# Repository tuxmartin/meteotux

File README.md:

meteotux
========

<!--
Screenshot weboveho rozhranni:
-

-->

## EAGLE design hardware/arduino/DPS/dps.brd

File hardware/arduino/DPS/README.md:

# !!! Stabilizator 7805 je obracene !!! #
Je potreba ho pri pajeni otocit (krajni dva piny).

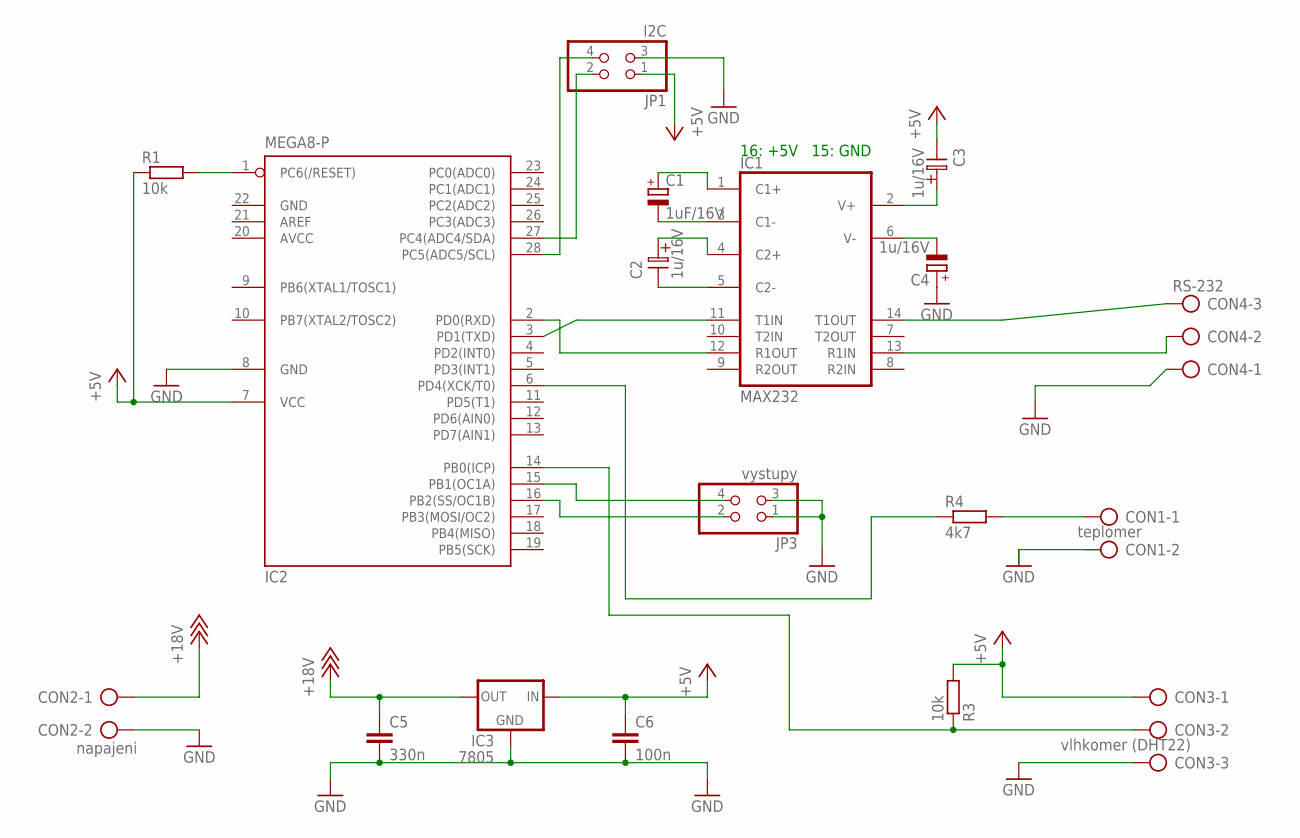
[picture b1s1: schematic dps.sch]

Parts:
C1: 1uF/16V; TT5D9
C2, C3: 1u/16V; ES-2,5L
C4: 1u/16V; TT5D9
C5: 330n; C025-025X050
C6: 100n; C025-025X050
CON1: teplomer; AK500/2
CON2: napajeni; AK500/2
CON3: vlhkomer (DHT22); AK500/3
CON4: RS-232; AK500/3
IC1: MAX232; DIL16
IC2: MEGA8-P; DIL28-3
IC3: 7805; 78XXL
JP1: I2C; 2X02
JP3: vystupy; 2X02
R1, R3: 10k; 0207/7
R4: 4k7; 0207/15

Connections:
+5V: C3.2, C6.1, CON3.1, IC1.16 (VCC), IC2.7 (VCC), IC3.IN, JP1.1, R1.1, R3.2
+18V: C5.1, CON2.1, IC3.OUT
AVCC: IC2.20 (AVCC)
GND: C4.+, C5.2, C6.2, CON2.2, CON3.3, CON4.1, IC1.15 (GND), IC2.8 (GND), IC2.22 (GND), IC3.GND, JP1.3, JP3.1, JP3.3
unnamed: IC1.12 (R1OUT), IC2.2 (PD0(RXD))
unnamed: C1.+, IC1.1 (C1+)
unnamed: C1.-, IC1.3 (C1-)
unnamed: C2.1, IC1.4 (C2+)
unnamed: C2.2, IC1.5 (C2-)
unnamed: C3.1, IC1.2 (V+)
unnamed: C4.-, IC1.6 (V-)
unnamed: IC1.11 (T1IN), IC2.3 (PD1(TXD))
unnamed: CON4.3, IC1.14 (T1OUT)
unnamed: CON4.2, IC1.13 (R1IN)
unnamed: IC2.28 (PC5(ADC5/SCL)), JP1.4
unnamed: CON1.1, R4.2
unnamed: IC2.16 (PB2(SS/OC1B)), JP3.2
unnamed: IC2.15 (PB1(OC1A)), JP3.4
unnamed: IC2.6 (PD4(XCK/T0)), R4.1
unnamed: IC2.27 (PC4(ADC4/SDA)), JP1.2
unnamed: CON3.2, IC2.14 (PB0(ICP)), R3.1
unnamed: IC2.1 (PC6(/RESET)), R1.2

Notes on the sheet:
16: +5V 15: GND

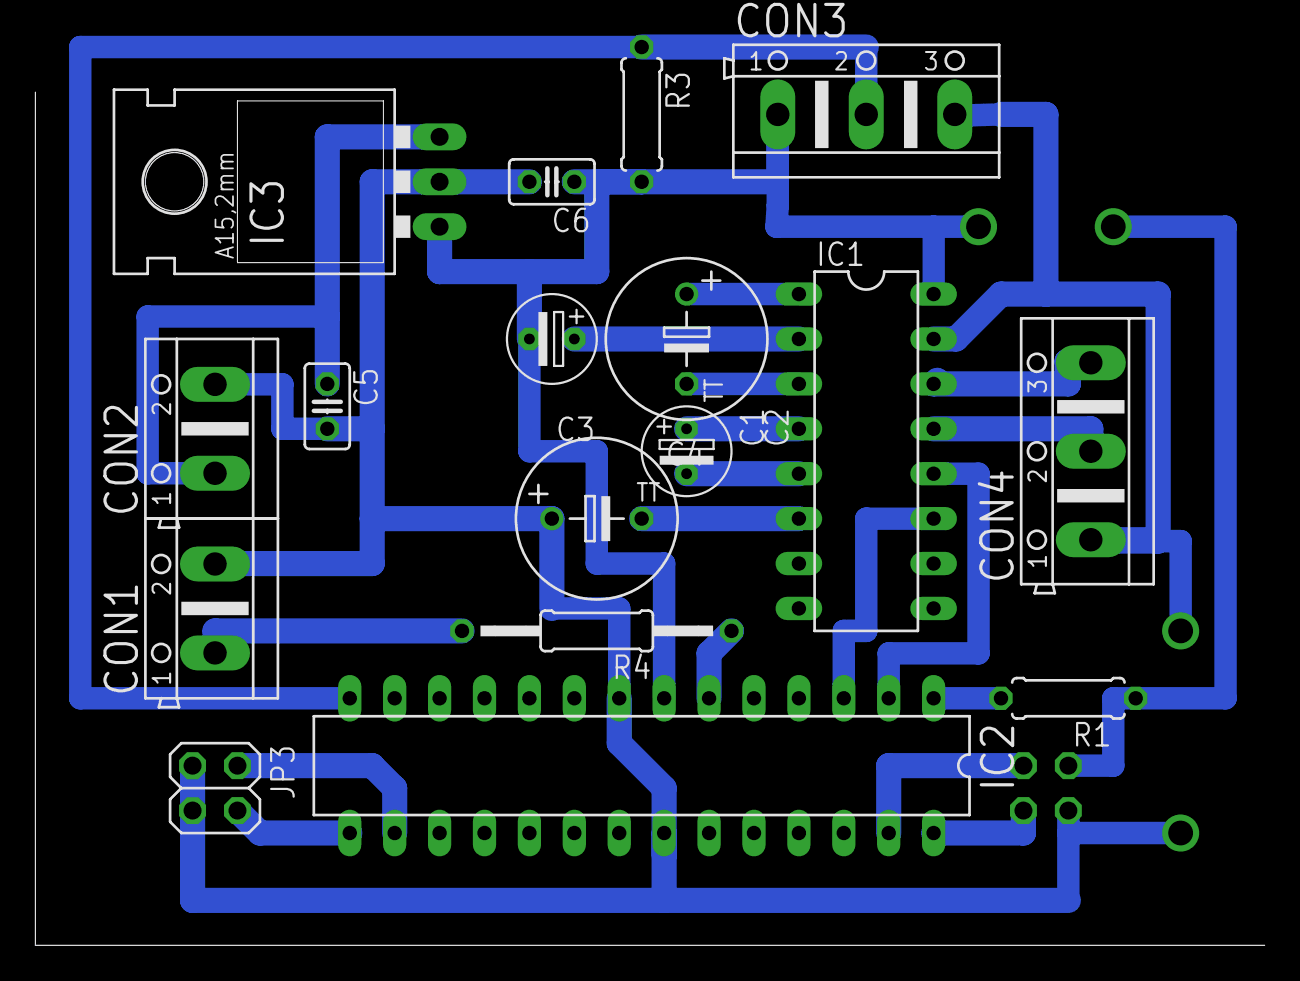
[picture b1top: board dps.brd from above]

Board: 2 copper layers, 69.5 x 48.2 mm, 18 parts (1 on the bottom side), 21 nets.

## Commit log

2013-02-12 +gitignore pro C, C++, Java
    Vice na https://github.com/github/gitignore
2013-02-12 +Jabber klient a SMACK xmpp knihovna
2013-02-12 +kod na komunikaci se seriovym portem (RS-232)
2013-02-12 +RSS (nacita hodnotu ze souboru)
2013-02-12 +skript na pasrsovani teploty z TMEP weboveho teplomeru
    http://code.google.com/p/tmep/
2013-02-22 +kod a ukazky pro arduino (prevzate z jineho projektu)
2013-02-22 OneWire knihovna nefunguje s novym Arduino IDE 1.0.1
2013-02-22 +DHT22 ukazkova knihovna: vlhkost a teplota OK
2013-02-22 format vypisu DHT-22 do RS-232 "23.10C 36.40%"
2013-02-22 funguje nekonecne cteni a vypisovani namerenych hodnot
2013-02-22 uprava nactenych hodnot a jejich rozdeleni do pole
2013-02-22 funguje nastaveni XMPP (Jabber) statusu s hodnotami
2013-02-22 kdyz jeste nejsou zmerene hodnoty, neaktualizuje status
2013-02-22 pomocny skript pro pripojeni projektu na localhost webserveru
2013-02-22 +sql tabulka pro ukladani namerenych hodnot
2013-02-23 +pridavani zaznamu pres URL do MySQL a zobrazeni vysledku
2013-02-23 +RSS - zobrazuje: teplota, vlhkost, teplota+vlhkost
2013-02-23 +www stranka s prehledem pocasi (vcetne RSS)
    historie, max, min, celkovy pocet, ...
2013-02-23 OK: mereni, XMPP aktualizace, HTTP aktualizace (do MySQL)
2013-02-23 zmenseni sloupce s rekordy
2013-02-23 +screenshot webove rozhranni
2013-02-23 chyba v SQL dotazu - spatne zobrazeni rekordnich teplot
2013-02-23 +navod na pouzit TMEP web app
2013-02-23 +podpora pro TMEP web app
2013-02-23 nalezena chyba v SQL dotazu pro hledani max teploty
2013-02-23 xmppClient - odstranen debug vypis na konzolu (sysout)
2013-02-23 +navod na spusteni vysledneho JAR souboru (je potreba JNI)
2013-02-24 Test odeslani dat do TMEP app. Overeni spravneho user-agenta.
2013-02-24 Prechod z Java 1.7 na Java 1.6: Debian stable nema Java 1.7.
2013-02-24 oprava komunikace s TMEP (poslani jineho http user-agenta)
2013-02-24 opraven preklep v komentari
2013-02-24 Odstranena knihovna Apache CommonsIO - nikde nebyla pouzita.
2013-02-24 +JAR soubory knihovny smack (xmpp), ktere kvuli gitignore chybely
2013-02-25 opraven komentar popisuju jeste neopravenou chybu (SQL MAX)
2013-03-01 phpinfo pro otestovani php curl modulu
2013-03-01 volani TMEP pres curl
2013-03-01 +diff pro TMEP 6.1 - posilani hodnoty jen z localhostu
    TMEP nepobezi v PC s teplomerem, ale na webhostingu.
    Protoze PC s teplomerem nebude mit verjenou IPv4 adresu,
    bylo by nutne vypnout v TMEPu kontrolu IP - za chvili by
    nam nekdo udelal v namerenych hodnotach pekny bordel...
    Proto TMEP prijima hodnoty pouze z localhostu a dalsi
    skript "teplota.php" na localhostu (webhostingu) bude
2013-03-01 +komentar k overovani IP u TMEP web app
2013-03-02 +firmware pro 8MHz ATmega8; optiboot zavadec; uprava Arduino IDE
2013-03-02 +schema plosneho spoje - nutno jeste zkontrolovat!
2013-03-10 program uz nevola TMEP, to si resi php aplikace
2013-03-10 nastaveni presunuto do samostatneho INI souboru
2013-05-20 +prejmenovana app v Jave, bude nasledovat app v Pythonu
2013-05-20 zaklad app v pythonu - nevyzkouseno!!!
2013-05-21 +APP (widget) pro Android. Funguje stazeni TXT pres HTTP a zobrazeni ve widgetu.
2013-05-21 upraveny widget pro pouziti http://teplomer.jicin.cz/
2013-05-21 pozadi z pruhledne na bilou - nebyl videt text
2013-05-21 funguje spravne cteni a vypisovani hodnot na stdout
2013-05-21 funguje posilani webove aplikaci; opravit neustale pridavani casu!
2013-05-21 webovy vystup pro android widget
2013-05-21 zpracovani vysledku v samostanem vlakne (kvuli zpozdeni mereni)
    bez druheho vlakna se prodluzovala doba mezi merenimi - cekalo se na
    dokonceni http pozadavku
2013-06-10 +logovani do syslogu
2013-06-10 oprava odsazeni radku syslogu
2013-07-15 -duplicitni ukladani do DB
2013-07-15 +komprese RSS - mensi prenos dat pro mobily
2013-07-15 hodnoty z TMEP tabulky; prechod na RSS2.0, vyhazeni zbytecnych elementu (mensi prenos dat)
2013-07-15 -tabulky z "index", nyni pouze odkaz a navod na RSS pro Andoid
2013-07-17 -skript neuklada datum poslane zarizenim
2013-07-17 +diff pro novy TMEP v6.3; -diff pro TMEP v 6.1
2013-07-17 +test odeslani teploty primo do TMEP bez meho skriptu
2013-07-17 +ve verzi bez parametru vraci RSS cas (hodiny a minuty)
2013-07-17 pridana chybejici mezera pred hodiny
2013-07-17 +ukazka widgetu na Android mobilu
2013-07-19 +stranka s boxem aktualnich hodnot - taha je z TMEP
    bude slouzit pro zobrazeni na webu v iframe
    pouziva curl :-/
2013-07-24 opravena verze plosneho spoje (cti README!!!)
    ve stare verzi byl spatne odpor z reset pinu ATmega8 (pin 1) na zem, spravne ma byt na +5V
    v nove verzi je obracene stabilizator 7805!!! a to jak ve schematu, tak na plosnem spoji - je nutne ho pri pajeni obratit !!!
2013-07-24 -screenshot stare verze webove rozhranni
2013-07-29 +funkcni verze pro OpenWrt (mereni a watchdog)
2013-08-01 +navod na Windows 7 gadget
2013-11-26 Kvuli chybe v DHT knihovne vracel pro zaporne teploty 32767.
    Chyba v pouzite DHT22 knihovne vraci pokud je namerena teplota mensi, nez 0°C "MAX_INT - namerenou teplotu". MAX_INT je na Arduinu 2 bajty = 32767 http://arduino.cc/en/Reference/Int
    Pro opravu lze vypocitat spravnou hodnotu.
    Napr. pro cislo 3276,4°C je teplota -0,3°C.
    TODO: opravit firmware pro Arduino (pouzit funkcni DHT22 knihovnu).
2013-11-26 +orpaveno odsazeni radku v python skriptu
2013-11-26 +opraveno odsazeni radku
2013-11-27 +pretypovani nemerene hodnoty - predtim program spadnul
2014-03-10 +watchdog do Arduina; pokud neprijde prikaz po rs232, po 15 minutach sepne rele
2015-12-02 Add a Bitdeli badge to README

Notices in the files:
parts and their libraries:
Copyright (C) Vlada 2004-2005
